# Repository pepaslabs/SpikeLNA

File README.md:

# SpikeLNA

A Low Noise Amplifier for measuring switcher spikes.

# Status

This board is untested.

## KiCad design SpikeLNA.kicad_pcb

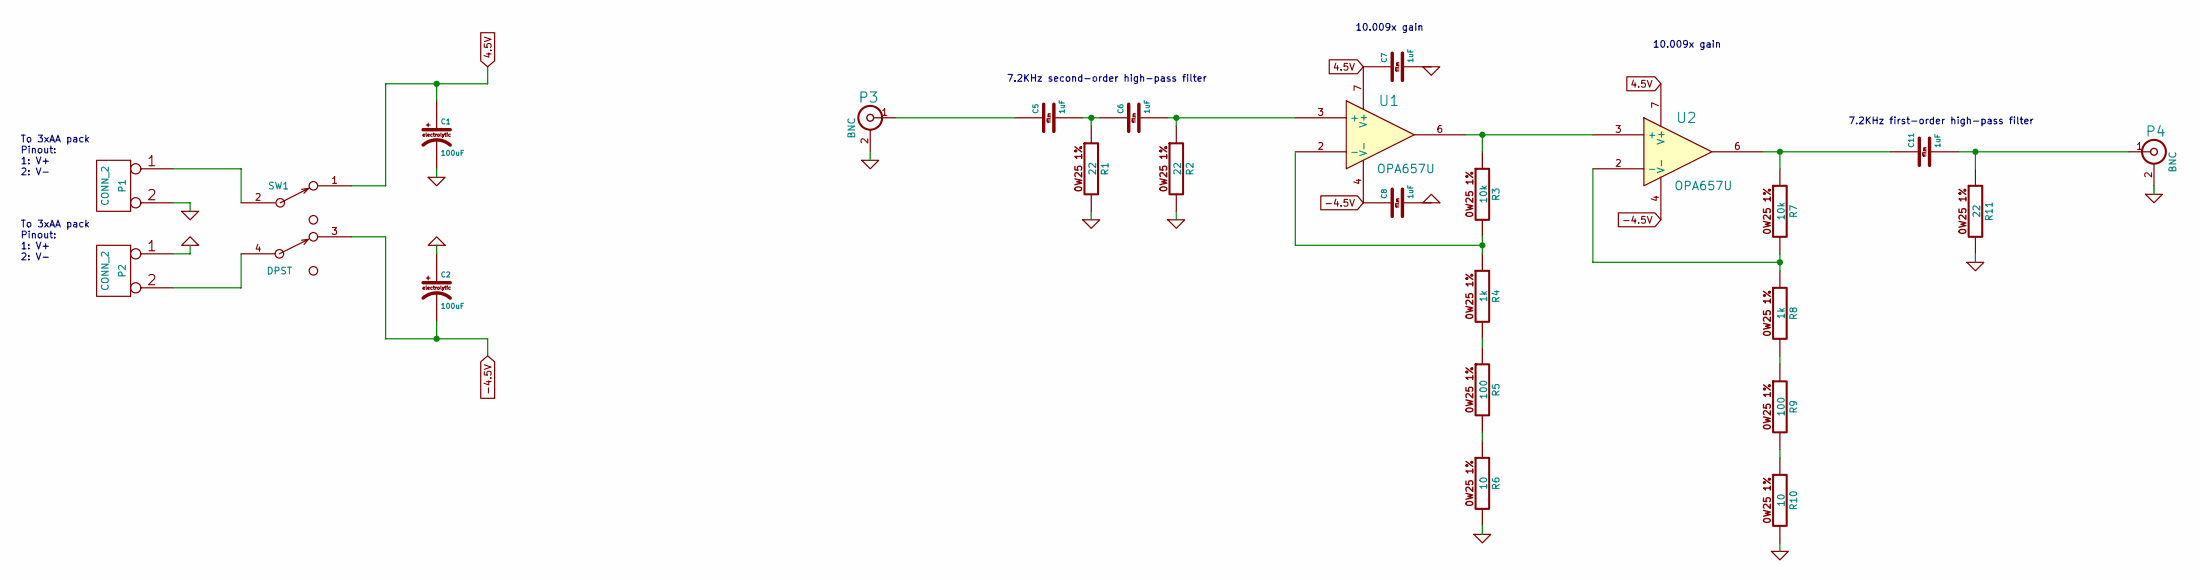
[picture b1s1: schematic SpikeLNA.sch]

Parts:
C1, C2: 100uF
C5, C6, C7, C8, C11: 1uF
P1, P2: CONN_2
P3, P4: BNC
R1, R2, R11: 22
R3, R7: 10k
R4, R8: 1k
R5, R9: 100
R6, R10: 10
SW1: DPST
U1, U2: OPA657U

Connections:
4.5V: C1.1, C7.1, SW1.1, U1.7 (V+), U2.7 (V+)
-4.5V: C2.2, C8.1, SW1.3, U1.4 (V-), U2.4 (V-)
GND: C1.2, C2.1, C7.2, C8.2, P1.2 (PM), P2.1, P3.2 (Ext), P4.2 (Ext), R1.2, R2.2, R6.2, R10.2, R11.2
unnamed: P2.2 (PM), SW1.4
unnamed: P1.1, SW1.2
unnamed: R3.2, R4.1, U1.2 (-)
unnamed: R5.2, R6.1
unnamed: R4.2, R5.1
unnamed: R3.1, U1.6, U2.3 (+)
unnamed: C6.2, R2.1, U1.3 (+)
unnamed: C5.1, P3.1 (In)
unnamed: C5.2, C6.1, R1.1
unnamed: C11.1, R7.1, U2.6
unnamed: C11.2, P4.1 (In), R11.1
unnamed: R7.2, R8.1, U2.2 (-)
unnamed: R8.2, R9.1
unnamed: R9.2, R10.1

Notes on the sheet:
7.2KHz second-order high-pass filter
10.009x gain
7.2KHz first-order high-pass filter
To 3xAA pack Pinout: 1: V+ 2: V-

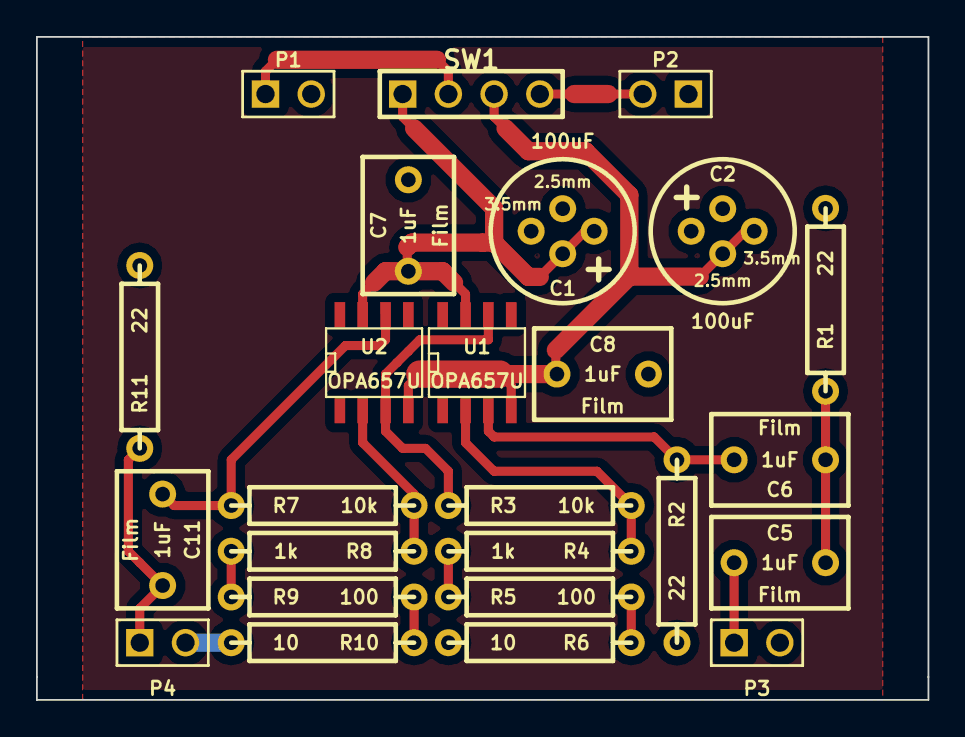
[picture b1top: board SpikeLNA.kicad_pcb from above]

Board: 2 copper layers, 49.5 x 36.8 mm, 25 parts (0 on the bottom side), 17 nets.

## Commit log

2014-07-07 first pass at this circuit.
2017-04-22 updating readme
